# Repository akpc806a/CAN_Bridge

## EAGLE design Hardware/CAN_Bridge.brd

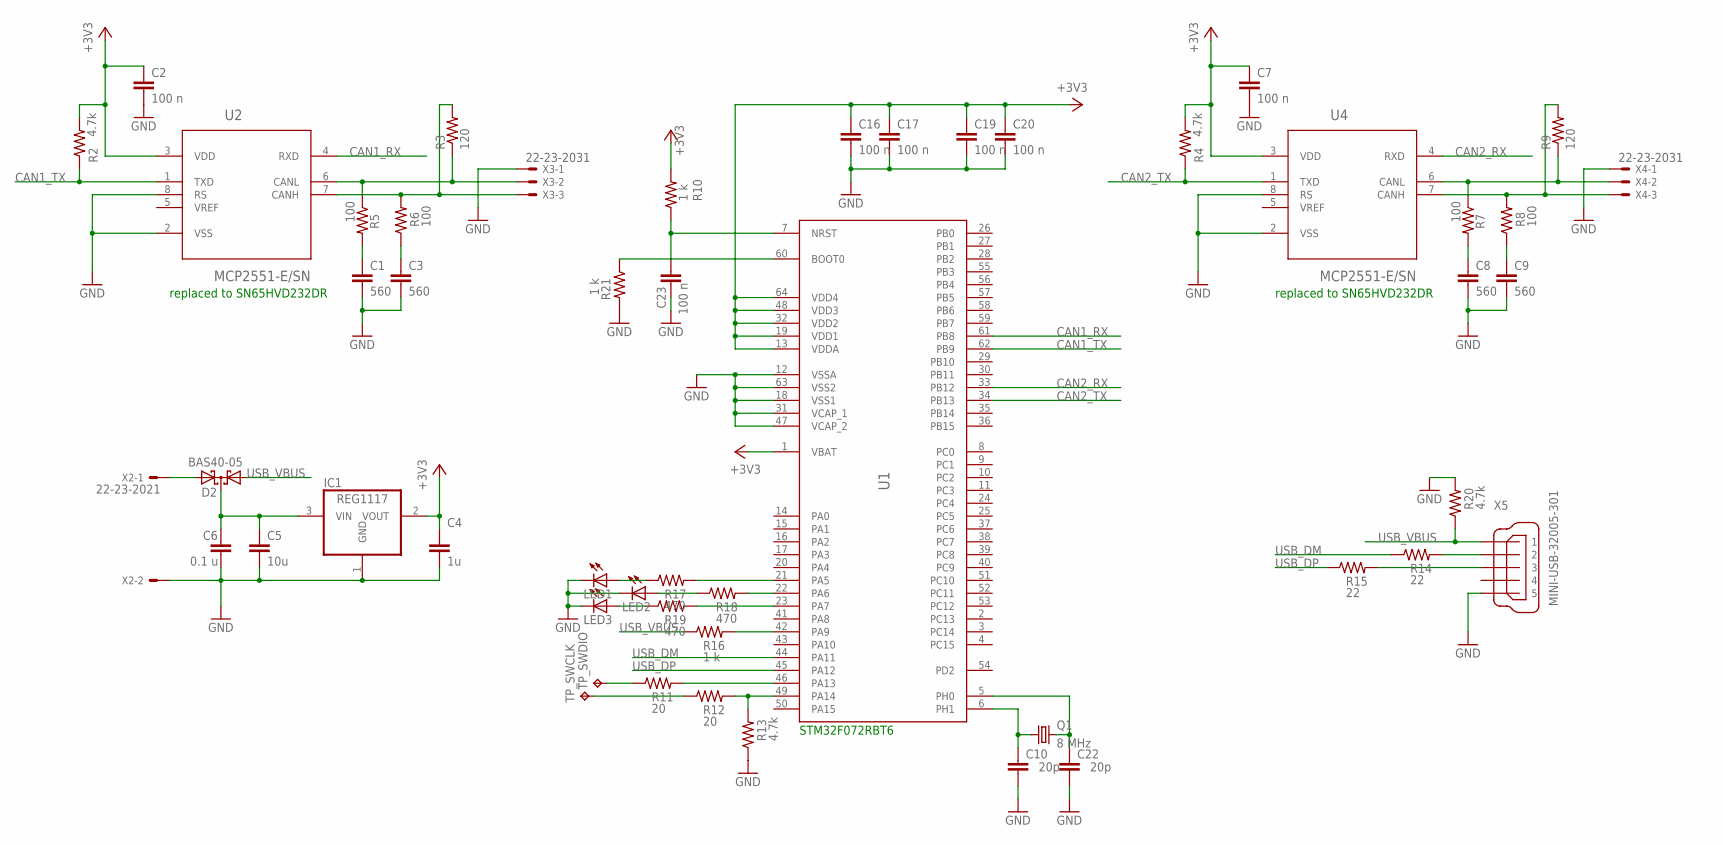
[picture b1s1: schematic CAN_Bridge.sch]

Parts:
C1, C3, C8, C9: 560; C0603
C2, C7, C16, C17, C19, C20, C23: 100 n; C0603
C4: 1u; C0603
C5: 10u; C1206
C6: 0.1 u; C0603
C10, C22: 20p; C0603
D2: BAS40-05; SOT23
IC1: REG1117; SOT223
LED1, LED2, LED3: LED_ESML0603; LED_SML0603
Q1: 8 MHz; SM49
R2, R4, R13, R20: 4.7k; R0603
R3, R9: 120; R0805
R5, R6, R7, R8: 100; R0603
R10, R16, R21: 1 k; R0603
R11, R12: 20; R0603
R14, R15: 22; R0603
R17, R18, R19: 470; R0603
TP_SWCLK: TPTP10SQ; TP10SQ
TP_SWDIO: TPTP10SQ; TP10SQ
U1: STM32F405XXSTM32F405XX; LQFP64
U2, U4: MCP2551-E/SN; SOIC127P600X175-8N
X2: 22-23-2021
X3, X4: 22-23-2031
X5: MINI-USB-32005-301; 32005-301

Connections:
+3V3: C2.1, C4.1, C7.1, C16.1, C17.1, C19.1, C20.1, IC1.2 (VOUT), R2.2, R4.2, R10.2, U1.1 (VBAT), U1.13 (VDDA), U1.19 (VDD1), U1.32 (VDD2), U1.48 (VDD3), U1.64 (VDD4), U2.3 (VDD), U4.3 (VDD)
CAN1_RX: U1.61 (PB8), U2.4 (RXD)
CAN1_TX: R2.1, U1.62 (PB9), U2.1 (TXD)
CAN2_RX: U1.33 (PB12), U4.4 (RXD)
CAN2_TX: R4.1, U1.34 (PB13), U4.1 (TXD)
GND: C1.2, C2.2, C3.2, C4.2, C5.2, C6.2, C7.2, C8.2, C9.2, C10.2, C16.2, C17.2, C19.2, C20.2, C22.2, C23.2, IC1.1 (GND), LED1.C, LED2.C, LED3.C, R13.1, R20.2, R21.2, U1.12 (VSSA), U1.18 (VSS1), U1.31 (VCAP_1), U1.47 (VCAP_2), U1.63 (VSS2), U2.2 (VSS), U2.8 (RS), U4.2 (VSS), U4.8 (RS), X2.2, X3.1, X4.1, X5.5
unnamed: R3.1, R5.1, U2.6 (CANL), X3.2
unnamed: R3.2, R6.2, U2.7 (CANH), X3.3
unnamed: C1.1, R5.2
unnamed: C3.1, R6.1
unnamed: R17.2, U1.21 (PA5)
unnamed: R7.1, R9.1, U4.6 (CANL), X4.2
unnamed: C5.1, C6.1, D2.3 (C), IC1.3 (VIN)
unnamed: R8.2, R9.2, U4.7 (CANH), X4.3
unnamed: C8.1, R7.2
unnamed: C9.1, R8.1
unnamed: R18.2, U1.22 (PA6)
unnamed: R19.2, U1.23 (PA7)
unnamed: LED1.A, R17.1
unnamed: LED2.A, R18.1
unnamed: LED3.A, R19.1
unnamed: R11.2, U1.46 (PA13)
unnamed: R12.2, R13.2, U1.49 (PA14)
unnamed: R11.1, TP_SWDIO.TP
unnamed: R12.1, TP_SWCLK.TP
unnamed: C23.1, R10.1, U1.7 (NRST)
unnamed: R21.1, U1.60 (BOOT0)
unnamed: D2.2 (A2), X2.1
unnamed: R16.2, U1.42 (PA9)
unnamed: R15.2, X5.3
unnamed: C22.1, Q1.2, U1.5 (PH0)
unnamed: C10.1, Q1.1, U1.6 (PH1)
unnamed: R14.2, X5.2
USB_DM: R14.1, U1.44 (PA11)
USB_DP: R15.1, U1.45 (PA12)
USB_VBUS: D2.1 (A1), R16.1, R20.1, X5.1

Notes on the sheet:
replaced to SN65HVD232DR
STM32F072RBT6

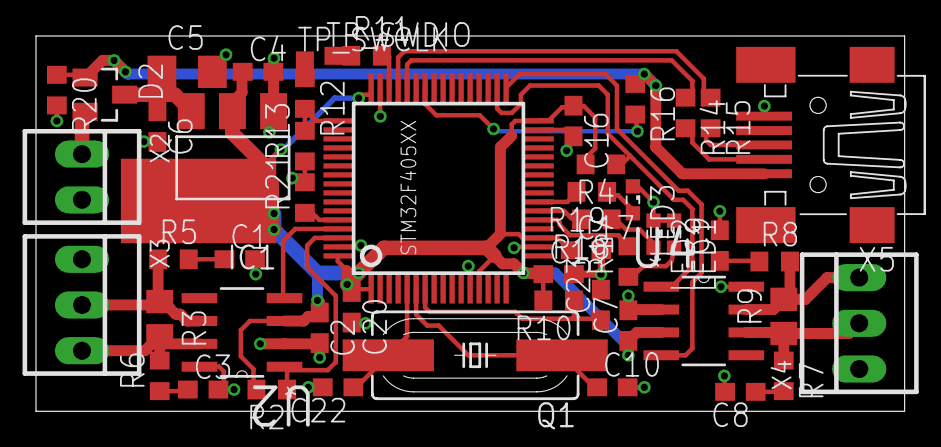
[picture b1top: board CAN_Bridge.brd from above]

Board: 2 copper layers, 48.3 x 20.8 mm, 51 parts (0 on the bottom side), 36 nets.

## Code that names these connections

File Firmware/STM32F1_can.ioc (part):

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Mcu.Name=STM32F105R(8-B-C)Tx
Mcu.Package=LQFP64
Mcu.UserName=STM32F105RBTx
PA11.Mode=Device_Only
PA11.Signal=USB_OTG_FS_DM
PA12.Mode=Device_Only
PA12.Signal=USB_OTG_FS_DP
PB12.Mode=Slave
PB12.Signal=CAN2_RX
PB13.Mode=Slave
PB13.Signal=CAN2_TX
PB8.Mode=Master
PB8.Signal=CAN1_RX
PB9.Mode=Master
PB9.Signal=CAN1_TX
PD0-OSC_IN.Mode=HSE-External-Oscillator
PD0-OSC_IN.Signal=RCC_OSC_IN
PD1-OSC_OUT.Mode=HSE-External-Oscillator
PD1-OSC_OUT.Signal=RCC_OSC_OUT
RCC.SYSCLKFreq_VALUE=72000000
RCC.SYSCLKSource=RCC_SYSCLKSOURCE_PLLCLK
board=STM32F1_can_

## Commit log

2016-08-08 Initial release, get ready for the Tindie
2016-08-08 Initial release, getting ready for Tindie
2016-08-16 some documentation corrections
2016-10-08 Firmware and software sources included
2017-10-03 3d model added
    3d design provided by Dott. Ing. Dario Armellin
2018-02-28 new revision of hardware (minor changes)
2025-02-24 adding hex file
2025-03-31 adding IOC (incomplete)
